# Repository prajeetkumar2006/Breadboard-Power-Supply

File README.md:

<h1 align="center">Breadboard Power Supply</h1>

## Description

Dual regulated power supply module converting 12 V DC to stable 5 V and 3.3 V outputs. Uses LM7805 for 5 V regulation and LM317 for adjustable 3.3 V output. Includes voltage selector jumpers, breadboard headers, and screw terminals for flexible output routing. Designed for powering microcontrollers, sensors, and prototyping circuits reliably.

## Hardware Used (BOM)

- DC Barrel Jack (with internal switch)
- SPDT Toggle Switch (Power ON/OFF)
- LM7805 Voltage Regulator (TO-220, 5V)
- LM317 Adjustable Voltage Regulator (TO-220, 3.3V)
- Resistors:
  - 330 Ω ×2 (LM317 voltage divider, LED current limit)
  - 560 Ω ×1 (LM317 voltage divider)
- Capacitors:
  - 10 µF Electrolytic ×1 (Input filtering)
  - 1 µF Electrolytic ×1 (3.3V output stability)
  - 0.1 µF Ceramic ×1 (5V output decoupling)
- LED ×1 (Power indicator)
- Jumper Headers (1×3, voltage selection)
- Pin Headers (1×2, breadboard output)
- Screw Terminal Connectors (2-pin, external output)
- PCB / Prototype Board

## Features
- Dual regulated outputs: 5V and 3.3V
- Selectable voltage routing via jumpers
- On-board power indication
- Designed for breadboard and external loads

## PCB Dimensions (Reference vs Current Design)

This power supply module is intended to be breadboard compatible.

### Reference Design Dimensions
- Overall Height: **49.7840 mm**
- Overall Width: **33.7822 mm**
- Side Extension Height: **40.6400 mm**

### Current PCB Design Dimensions
- Overall Height: **52.4256 mm**
- Overall Width: **31.0388 mm**
- Side Extension Height: **45.7708 mm**

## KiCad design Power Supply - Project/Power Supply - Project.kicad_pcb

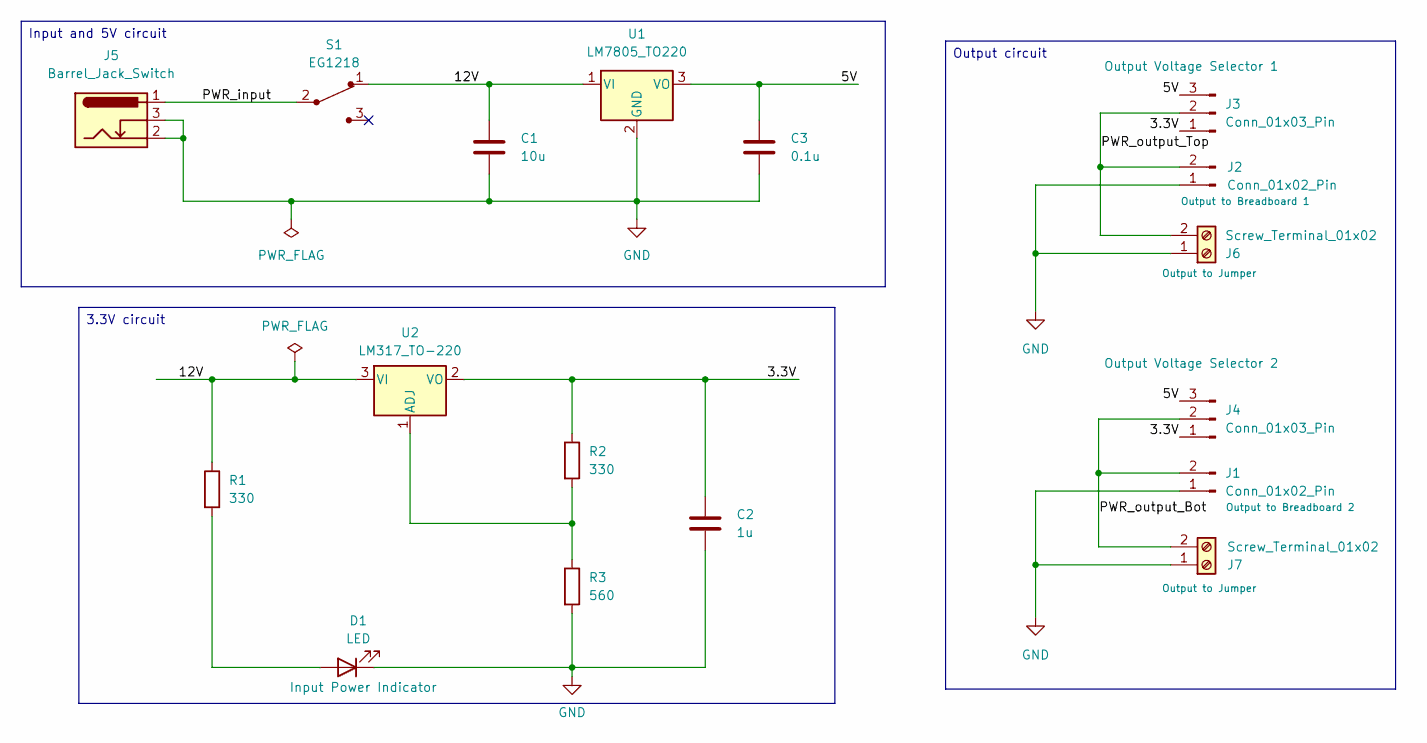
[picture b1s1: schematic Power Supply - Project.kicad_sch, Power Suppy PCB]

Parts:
C1: 10u; C_Disc_D3.0mm_W1.6mm_P2.50mm
C2: 1u; C_Disc_D3.0mm_W1.6mm_P2.50mm
C3: 0.1u; C_Disc_D3.0mm_W1.6mm_P2.50mm
D1: LED; LED_D5.0mm
J1, J2: Conn_01x02_Pin; PinHeader_1x02_P2.54mm_Vertical
J3, J4: Conn_01x03_Pin; PinHeader_1x03_P2.54mm_Vertical
J5: Barrel_Jack_Switch; BarrelJack_Horizontal
J6, J7: Screw_Terminal_01x02; TerminalBlock_bornier-2_P5.08mm
R1, R2: 330; R_Axial_DIN0204_L3.6mm_D1.6mm_P7.62mm_Horizontal
R3: 560; R_Axial_DIN0204_L3.6mm_D1.6mm_P7.62mm_Horizontal
S1: EG1218; Switch_Slide_11.6x4mm_EG1218; MPN EG1218; Digi-Key_PN EG1903-ND
U1: LM7805_TO220; TO-220-3_Vertical
U2: LM317_TO-220; TO-220-3_Vertical

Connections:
/3.3V: C2.1, J3.1, J4.1, R2.1, U2.2 (VO)
/5V: C3.1, J3.3, J4.3, U1.3 (VO)
/12V: C1.1, R1.1, S1.1, U1.1 (VI), U2.3 (VI)
/PWR_input: J5.1, S1.2
/PWR_output_Bot: J1.2, J4.2, J7.2
/PWR_output_Top: J2.2, J3.2, J6.2
GND: C1.2, C2.2, C3.2, D1.1 (K), J1.1, J2.1, J5.2, J5.3, J6.1, J7.1, R3.2, U1.2 (GND)
unnamed: D1.2 (A), R1.2
unnamed: R2.2, R3.1, U2.1 (ADJ)

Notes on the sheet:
Input and 5V circuit
3.3V circuit
Output circuit

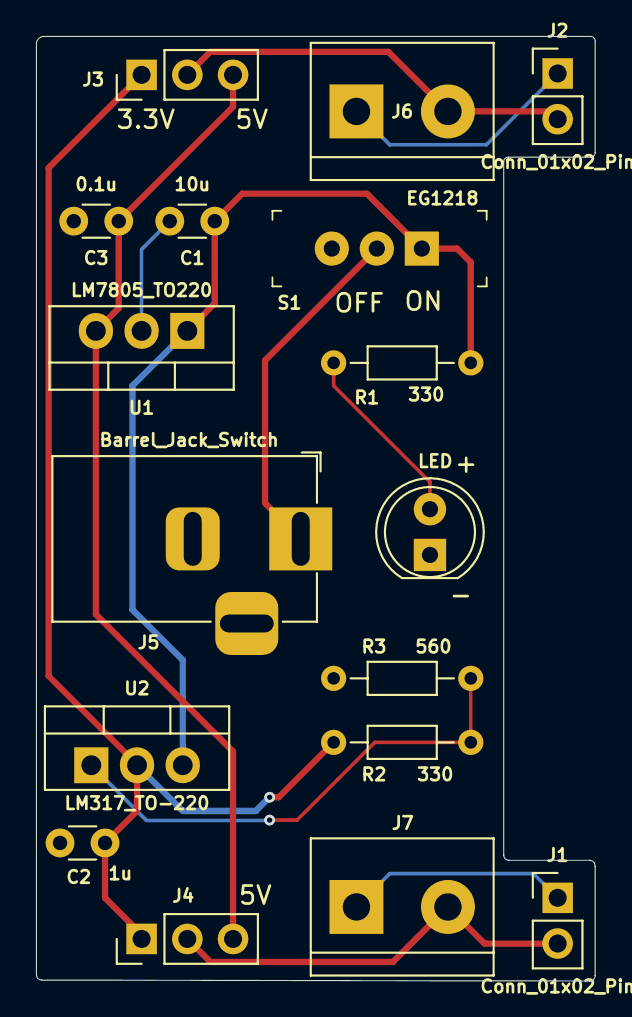
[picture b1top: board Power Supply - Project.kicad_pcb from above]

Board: 2 copper layers, 31.0 x 52.5 mm, 17 parts (0 on the bottom side), 9 nets.

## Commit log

2025-12-31 Enhance README with project details and specifications
    Added detailed description, hardware components, features, and PCB dimensions for the Breadboard Power Supply.
